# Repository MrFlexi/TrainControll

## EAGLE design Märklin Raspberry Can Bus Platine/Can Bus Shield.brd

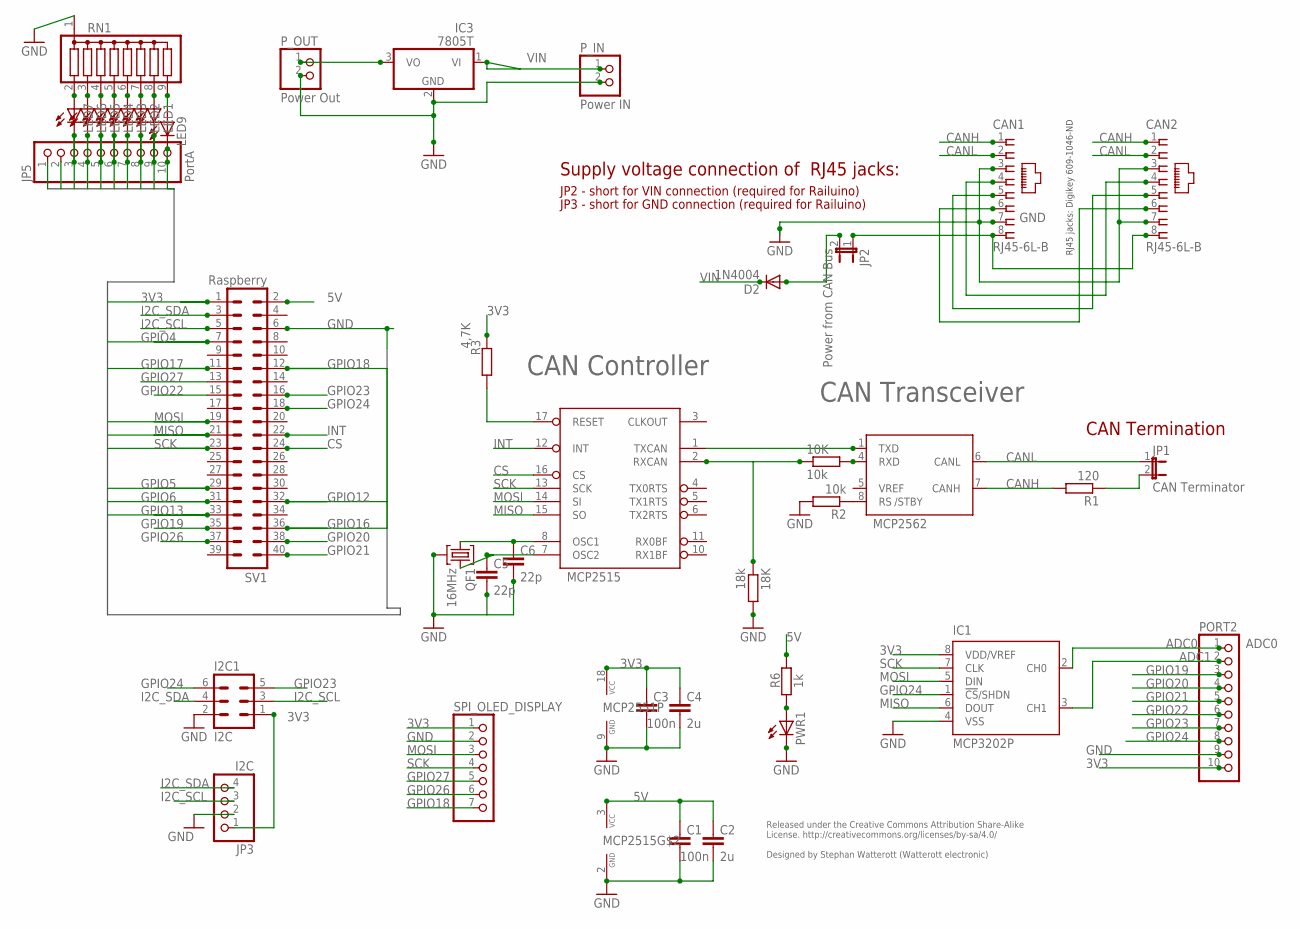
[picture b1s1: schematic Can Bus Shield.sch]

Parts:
10K: 10k; R2010
18K: 18k; R2010
C1, C3: 100n; C1812
C2, C4: 2u; C1812
C5: 22p; C025-030X050
C6: 22p; C025-025X050
CAN1, CAN2: RJ45-6L-B; RJ45-NO-SHIELD
D2: 1N4004; DO41-10
I2C1: I2C; 06H
IC1: MCP3202P; DIL8
IC3: 7805T; TO220H
JP1: CAN Terminator; JP1
JP2: Power from CAN Bus; JP1
JP3: I2C; 1X04
JP5: PortA; 1X10
LED1, LED2, LED3, LED4, LED5, LED6, LED7, LED9: LEDSML1206; SML1206
MCP2515: MCP2562; DIL08
MCP2551: MCP2515; DIL18
PORT2: PINHD-1X10; 1X10
PWR1: LEDSMT1206; 1206
P_IN: Power IN; 1X02
P_OUT: Power Out; 1X02
QF1: 16MHz; HC49U
R1: 120; R2010
R2: 10k; R2010
R3: 4,7K; R2010
R6: 1k; R2010
RN1: G08R; SIL9
SPI_OLED_DISPLAY: PINHD-1X7; 1X07
SV1: Raspberry; ML40

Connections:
3V3: C3.1, C4.1, I2C1.1, IC1.8 (VDD/VREF), JP3.1, JP5.1, MCP2551.18 (VCC), PORT2.10, R3.1, SPI_OLED_DISPLAY.1, SV1.1
5V: C1.1, C2.1, IC3.3 (VO), MCP2515.3 (VCC), P_OUT.1, R6.1, SV1.2
ADC0: IC1.2 (CH0), PORT2.1
ADC1: IC1.3 (CH1), PORT2.2
CANH: CAN1.1, CAN2.1, MCP2515.7 (CANH), R1.2
CANL: CAN1.2, CAN2.2, JP1.1, MCP2515.6 (CANL)
CAN_TX: MCP2515.1 (TXD), MCP2551.1 (TXCAN)
CS: MCP2551.16 (CS), SV1.24
GND: 18K.2, C1.2, C2.2, C3.2, C4.2, C5.2, C6.2, CAN1.3, CAN1.7, CAN2.3, CAN2.7, I2C1.2, IC1.4 (VSS), IC3.2 (GND), JP3.2, JP5.2, MCP2515.2 (GND), MCP2551.9 (GND), PORT2.9, PWR1.C, P_IN.2, P_OUT.2, QF1.2, R2.2, RN1.1, SPI_OLED_DISPLAY.2, SV1.6
GPIO4: JP5.10, LED9.C, SV1.7
GPIO5: JP5.9, LED1.C, SV1.29
GPIO6: JP5.8, LED2.C, SV1.31
GPIO12: JP5.7, LED3.C, SV1.32
GPIO13: JP5.6, LED4.C, SV1.33
GPIO16: JP5.5, LED5.C, SV1.36
GPIO17: JP5.4, LED6.C, SV1.11
GPIO18: JP5.3, LED7.C, SPI_OLED_DISPLAY.7, SV1.12
GPIO19: PORT2.3, SV1.35
GPIO20: PORT2.4, SV1.38
GPIO21: PORT2.5, SV1.40
GPIO22: PORT2.6, SV1.15
GPIO23: I2C1.5, PORT2.7, SV1.16
GPIO24: I2C1.6, IC1.1 (!CS!/SHDN), PORT2.8, SV1.18
GPIO26: SPI_OLED_DISPLAY.6, SV1.37
GPIO27: SPI_OLED_DISPLAY.5, SV1.13
I2C_SCL: I2C1.3, JP3.3, SV1.5
I2C_SDA: I2C1.4, JP3.4, SV1.3
INT: MCP2551.12 (INT), SV1.22
MISO: IC1.6 (DOUT), MCP2551.15 (SO), SV1.21
MOSI: IC1.5 (DIN), MCP2551.14 (SI), SPI_OLED_DISPLAY.3, SV1.19
unnamed: 10K.1, 18K.1, MCP2551.2 (RXCAN)
unnamed: LED9.A, RN1.9
unnamed: LED1.A, RN1.8
unnamed: LED2.A, RN1.7
unnamed: LED3.A, RN1.6
unnamed: CAN1.8, CAN2.8, JP2.1
unnamed: MCP2515.8 (RS), R2.1
unnamed: LED4.A, RN1.5
unnamed: JP1.2, R1.1
unnamed: LED5.A, RN1.4
unnamed: LED6.A, RN1.3
unnamed: LED7.A, RN1.2
unnamed: MCP2551.17 (RESET), R3.2
unnamed: 10K.2, MCP2515.4 (RXD)
unnamed: PWR1.A, R6.2
unnamed: D2.A, JP2.2
unnamed: CAN1.4, CAN2.4
unnamed: CAN1.5, CAN2.5
unnamed: CAN1.6, CAN2.6
OSC1: C6.1, MCP2551.8 (OSC1), QF1.1
OSC2: C5.1, MCP2551.7 (OSC2), QF1.3
SCK: IC1.7 (CLK), MCP2551.13 (SCK), SPI_OLED_DISPLAY.4, SV1.23
VIN: D2.C, IC3.1 (VI), P_IN.1

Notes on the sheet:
Released under the Creative Commons Attribution Share-Alike License. http://creativecommons.org/licenses/by-sa/4.0/ Designed by Stephan Watterott (Watterott electronic)
CAN Termination
Supply voltage connection of RJ45 jacks:
JP3 - short for GND connection (required for Railuino)
JP2 - short for VIN connection (required for Railuino)
RJ45 jacks: Digikey 609-1046-ND
CAN Controller
CAN Transceiver
/STBY

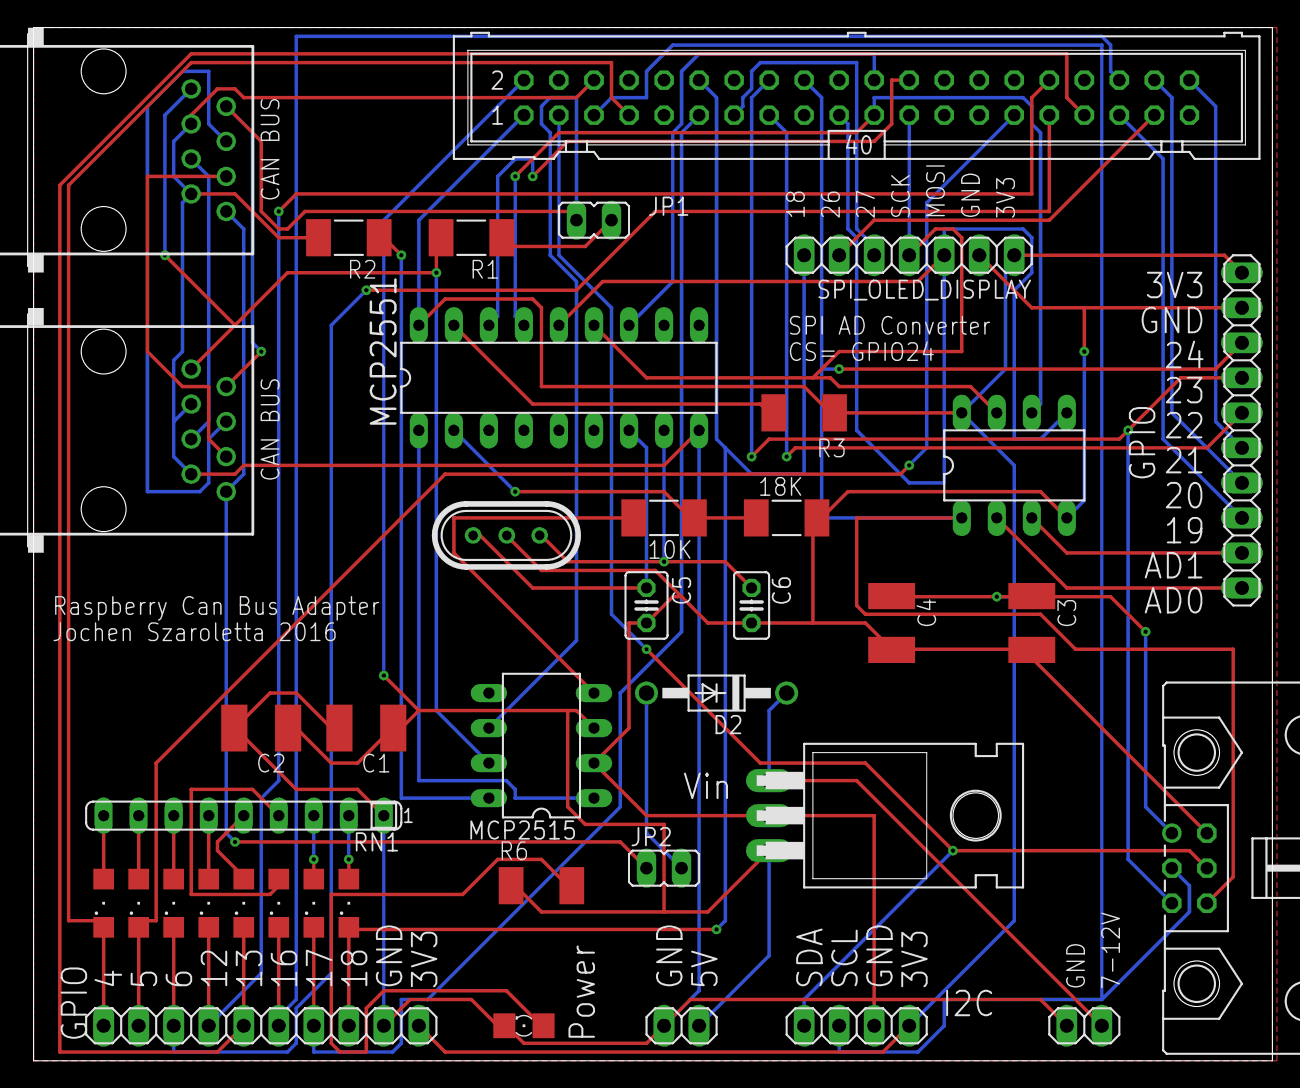
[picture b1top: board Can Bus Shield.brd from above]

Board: 2 copper layers, 90.3 x 74.9 mm, 40 parts (0 on the bottom side), 53 nets.

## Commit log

2017-11-13 Version 0.0
2017-11-13 Version 0.1
2017-11-15 Version 1.1
2017-11-16 Version 1.2
    Umbau Daten Binding auf Named Modells
    Modularisierung
2017-11-25 Version 1.2: new UDP class
2017-11-25 Version 1.3: Wechsel der Lokomotive per Carousel
2017-11-25 Version 1.3: Key Error Dict fixed
2017-12-06 Lok Liste im Admin Modus eingebaut
2017-12-06 CPU handling optimiert
2017-12-08 Version 1.4: LokListe in eigenes emit event ausgelagert.
2017-12-14 Neu: Gleisbild anlegen ( erste Versuche )
2017-12-14 Neu: Gleisbild anlegen + JSON Model + Bereiche wieder anzeigen
2017-12-16 Lokliste wird aus File gelesen
2017-12-16 Lokliste: update File handling
2017-12-18 Gleisplan als File SAVE
2017-12-18 Gleisplan als Modell + Save + Neue Weiche
2017-12-21 Gleisplan UI5 Image Map
2018-02-10 Neue Seite TrackShow Image Map wird dynamisch aus JSON Object aufgebaut Event Listener
2018-02-12 Gleisplan Turnout fertiggestellt Datentransport UI --> Modell --> UI
2018-02-16 Client Class changed to static Socketio disconnect
2018-02-21 XML Fragments in seperate Folder
2018-07-22 Documentation added
2018-07-22 NodeMcu sources added
2018-08-30 New XML Main View
2018-08-30 new status blocked/available
2018-08-30 Icons Changes Lok Selection Dialog
2018-08-30 Stable Version
2018-08-31 TNT Page is now new home screen
2018-08-31 User Management
2018-08-31 User Management with selection Dialog
2019-03-16 jaja
2021-01-02 Python 3.9
2021-01-02 Bump notebook from 6.1.3 to 6.1.5
    Bumps [notebook](https://github.com/jupyter/jupyterhub) from 6.1.3 to 6.1.5.
    - [Release notes](https://github.com/jupyter/jupyterhub/releases)
    - [Changelog](https://github.com/jupyterhub/jupyterhub/blob/master/CHECKLIST-Release.md)
    - [Commits](https://github.com/jupyter/jupyterhub/commits)
2021-01-02 Bump pillow from 7.0.0 to 7.1.0
    Bumps [pillow](https://github.com/python-pillow/Pillow) from 7.0.0 to 7.1.0.
    - [Release notes](https://github.com/python-pillow/Pillow/releases)
    - [Changelog](https://github.com/python-pillow/Pillow/blob/master/CHANGES.rst)
    - [Commits](https://github.com/python-pillow/Pillow/compare/7.0.0...7.1.0)
2021-01-04 bugfixes
2021-01-07 Luma OLED
2021-01-07 even better now
2021-01-10 Update Anleitung
2021-01-14 Stable1
2021-01-30 Show IP
2021-02-01 less bugs
2021-02-02 O.K.
2021-02-02 Bump bleach from 3.1.5 to 3.3.0
    Bumps [bleach](https://github.com/mozilla/bleach) from 3.1.5 to 3.3.0.
    - [Release notes](https://github.com/mozilla/bleach/releases)
    - [Changelog](https://github.com/mozilla/bleach/blob/master/CHANGES)
    - [Commits](https://github.com/mozilla/bleach/compare/v3.1.5...v3.3.0)
2021-02-03 Functions
2021-02-03 Direction change O.K.
2021-02-03 gevent installiert
2021-02-05 tests
2021-02-05 speed ok
2021-02-05 ja ja
2021-02-07 menu to json file navigation tile to fragment
2021-02-11 Weichen OK
2021-02-13 done
2021-02-24 tensorflow deinstalled
2021-03-02 Navigation updated
2021-03-02 Track
2021-03-02 Display
2021-03-02 together
2021-03-02 track events klappen noch nicht
2021-03-05 nix gut
2021-03-05 fabricjs html library included
2021-03-08 Fabric JS included
2021-03-08 fabricjs
2021-03-09 fabric save + load
2021-03-09 fabric number + toggle turnout
2021-03-13 fabric js with event and line color change
2021-03-16 snap to grid
2021-03-19 Bump pillow from 8.1.0 to 8.1.1
    Bumps [pillow](https://github.com/python-pillow/Pillow) from 8.1.0 to 8.1.1.
    - [Release notes](https://github.com/python-pillow/Pillow/releases)
    - [Changelog](https://github.com/python-pillow/Pillow/blob/master/CHANGES.rst)
    - [Commits](https://github.com/python-pillow/Pillow/compare/8.1.0...8.1.1)
2021-03-20 Bump jinja2 from 2.11.2 to 2.11.3
    Bumps [jinja2](https://github.com/pallets/jinja) from 2.11.2 to 2.11.3.
    - [Release notes](https://github.com/pallets/jinja/releases)
    - [Changelog](https://github.com/pallets/jinja/blob/master/CHANGES.rst)
    - [Commits](https://github.com/pallets/jinja/compare/2.11.2...2.11.3)
2021-03-21 fabricjs: to gleisplan.js HangMan removed
2021-03-22 Groups not OK
2021-03-30 Bump pygments from 2.6.1 to 2.7.4
    Bumps [pygments](https://github.com/pygments/pygments) from 2.6.1 to 2.7.4.
    - [Release notes](https://github.com/pygments/pygments/releases)
    - [Changelog](https://github.com/pygments/pygments/blob/master/CHANGES)
    - [Commits](https://github.com/pygments/pygments/compare/2.6.1...2.7.4)
2021-05-08 Bump eventlet from 0.30.0 to 0.31.0
    Bumps [eventlet](https://github.com/eventlet/eventlet) from 0.30.0 to 0.31.0.
    - [Release notes](https://github.com/eventlet/eventlet/releases)
    - [Changelog](https://github.com/eventlet/eventlet/blob/master/NEWS)
    - [Commits](https://github.com/eventlet/eventlet/compare/v0.30.0...v0.31.0)
2021-06-02 Bump urllib3 from 1.25.10 to 1.26.5
    Bumps [urllib3](https://github.com/urllib3/urllib3) from 1.25.10 to 1.26.5.
    - [Release notes](https://github.com/urllib3/urllib3/releases)
    - [Changelog](https://github.com/urllib3/urllib3/blob/main/CHANGES.rst)
    - [Commits](https://github.com/urllib3/urllib3/compare/1.25.10...1.26.5)
    ---
    updated-dependencies:
2021-06-08 Bump pillow from 8.1.0 to 8.2.0
    Bumps [pillow](https://github.com/python-pillow/Pillow) from 8.1.0 to 8.2.0.
    - [Release notes](https://github.com/python-pillow/Pillow/releases)
    - [Changelog](https://github.com/python-pillow/Pillow/blob/master/CHANGES.rst)
    - [Commits](https://github.com/python-pillow/Pillow/compare/8.1.0...8.2.0)
    ---
    updated-dependencies:
2021-08-09 Bump pywin32 from 228 to 301
    Bumps [pywin32](https://github.com/mhammond/pywin32) from 228 to 301.
    - [Release notes](https://github.com/mhammond/pywin32/releases)
    - [Changelog](https://github.com/mhammond/pywin32/blob/master/CHANGES.txt)
    - [Commits](https://github.com/mhammond/pywin32/commits)
    ---
    updated-dependencies:
2021-08-23 Bump notebook from 6.1.3 to 6.4.1
    Bumps [notebook](http://jupyter.org) from 6.1.3 to 6.4.1.
    ---
    updated-dependencies:
    - dependency-name: notebook
    dependency-type: direct:production
    ...
2021-11-13 so la la
2021-11-14 10 Weichen
2021-11-14 Edit/Play
2021-11-16 Gleisplan in File ausgelagert
2021-11-16 V1.0
2021-11-16 code cleanup
2021-11-16 some fixes
2021-11-17 JoJo
2021-11-17 ESP32
2021-11-18 MQTT intruduced
2021-11-28 Resize Canvas
2021-11-28 Mqtt On
2021-11-28 something
2021-11-28 Save Gleisplan
2021-12-05 COORS enabled
2021-12-06 Ionic Integration
2021-12-11 Linde
2021-12-11 Bump pillow from 7.0.0 to 8.3.2
    Bumps [pillow](https://github.com/python-pillow/Pillow) from 7.0.0 to 8.3.2.
    - [Release notes](https://github.com/python-pillow/Pillow/releases)
    - [Changelog](https://github.com/python-pillow/Pillow/blob/master/CHANGES.rst)
    - [Commits](https://github.com/python-pillow/Pillow/compare/7.0.0...8.3.2)
    ---
    updated-dependencies:
2021-12-11 mqtt bugfix
2021-12-11 Index.html
2021-12-16 Cleanup
2021-12-16 Mqtt update
2021-12-16 Code
2021-12-16 OnLock value changed
2021-12-16 Wait till network available
2021-12-17 BR50 BR151 added
2021-12-19 Terminal display
2021-12-19 Terminal
2021-12-19 kein event
2021-12-19 delay first event 2 seconds
2021-12-20 MQTT O.K.
2021-12-21 HTTP API, Logging
2021-12-21 yea...
2021-12-22 better Pics
2021-12-22 Linux changes
2021-12-22 Even better
2021-12-22 better
2021-12-23 mostly better
2021-12-23 UI Improvements
2022-01-13 Bump pillow from 7.0.0 to 9.0.0
    Bumps [pillow](https://github.com/python-pillow/Pillow) from 7.0.0 to 9.0.0.
    - [Release notes](https://github.com/python-pillow/Pillow/releases)
    - [Changelog](https://github.com/python-pillow/Pillow/blob/main/CHANGES.rst)
    - [Commits](https://github.com/python-pillow/Pillow/compare/7.0.0...9.0.0)
    ---
    updated-dependencies:
2022-01-21 Bump ipython from 7.17.0 to 7.31.1
    Bumps [ipython](https://github.com/ipython/ipython) from 7.17.0 to 7.31.1.
    - [Release notes](https://github.com/ipython/ipython/releases)
    - [Commits](https://github.com/ipython/ipython/compare/7.17.0...7.31.1)
    ---
    updated-dependencies:
    - dependency-name: ipython
2022-03-12 Bump pillow from 7.0.0 to 9.0.1
    Bumps [pillow](https://github.com/python-pillow/Pillow) from 7.0.0 to 9.0.1.
    - [Release notes](https://github.com/python-pillow/Pillow/releases)
    - [Changelog](https://github.com/python-pillow/Pillow/blob/main/CHANGES.rst)
    - [Commits](https://github.com/python-pillow/Pillow/compare/7.0.0...9.0.1)
    ---
    updated-dependencies:
2022-04-06 Bump notebook from 6.1.3 to 6.4.10
    Bumps [notebook](http://jupyter.org) from 6.1.3 to 6.4.10.
    ---
    updated-dependencies:
    - dependency-name: notebook
    dependency-type: direct:production
    ...
2022-06-16 Bump notebook from 6.1.3 to 6.4.12
    Bumps [notebook](http://jupyter.org) from 6.1.3 to 6.4.12.
    ---
    updated-dependencies:
    - dependency-name: notebook
    dependency-type: direct:production
    ...
2022-06-22 Bump numpy from 1.18.1 to 1.22.0
    Bumps [numpy](https://github.com/numpy/numpy) from 1.18.1 to 1.22.0.
    - [Release notes](https://github.com/numpy/numpy/releases)
    - [Changelog](https://github.com/numpy/numpy/blob/main/doc/HOWTO_RELEASE.rst)
    - [Commits](https://github.com/numpy/numpy/compare/v1.18.1...v1.22.0)
    ---
    updated-dependencies:
2022-07-29 Bump mistune from 0.8.4 to 2.0.3
    Bumps [mistune](https://github.com/lepture/mistune) from 0.8.4 to 2.0.3.
    - [Release notes](https://github.com/lepture/mistune/releases)
    - [Changelog](https://github.com/lepture/mistune/blob/master/docs/changes.rst)
    - [Commits](https://github.com/lepture/mistune/compare/v0.8.4...v2.0.3)
    ---
    updated-dependencies:
2022-08-10 Bump nbconvert from 5.6.1 to 6.3.0
    Bumps [nbconvert](https://github.com/jupyter/nbconvert) from 5.6.1 to 6.3.0.
    - [Release notes](https://github.com/jupyter/nbconvert/releases)
    - [Commits](https://github.com/jupyter/nbconvert/compare/5.6.1...6.3.0)
    ---
    updated-dependencies:
    - dependency-name: nbconvert
2022-08-23 Bump nbconvert from 5.6.1 to 6.5.1
    Bumps [nbconvert](https://github.com/jupyter/nbconvert) from 5.6.1 to 6.5.1.
    - [Release notes](https://github.com/jupyter/nbconvert/releases)
    - [Commits](https://github.com/jupyter/nbconvert/compare/5.6.1...6.5.1)
    ---
    updated-dependencies:
    - dependency-name: nbconvert
2022-09-07 Fixed cross origin
2022-09-10 SBB Cargo DCC Addr = 10
2022-11-22 Bump pillow from 7.0.0 to 9.3.0
    Bumps [pillow](https://github.com/python-pillow/Pillow) from 7.0.0 to 9.3.0.
    - [Release notes](https://github.com/python-pillow/Pillow/releases)
    - [Changelog](https://github.com/python-pillow/Pillow/blob/main/CHANGES.rst)
    - [Commits](https://github.com/python-pillow/Pillow/compare/7.0.0...9.3.0)
    ---
    updated-dependencies:
2022-12-08 Bump certifi from 2020.6.20 to 2022.12.7
    Bumps [certifi](https://github.com/certifi/python-certifi) from 2020.6.20 to 2022.12.7.
    - [Release notes](https://github.com/certifi/python-certifi/releases)
    - [Commits](https://github.com/certifi/python-certifi/compare/2020.06.20...2022.12.07)
    ---
    updated-dependencies:
    - dependency-name: certifi
2023-09-23 OLED Fixes
2023-09-23 New UI5 Icons
2023-09-23 Display Page0 activated
2023-09-24 LED Indicators
2023-09-24 LED blink pattern
2023-09-29 Platine
2023-09-30 M5Stack + Mqtt
2023-09-30 fixes
2023-09-30 bugfix
2023-10-03 mqtt last will
2023-10-03 udp test
2023-10-03 udp sniffer
2024-11-09 GetLokList API
